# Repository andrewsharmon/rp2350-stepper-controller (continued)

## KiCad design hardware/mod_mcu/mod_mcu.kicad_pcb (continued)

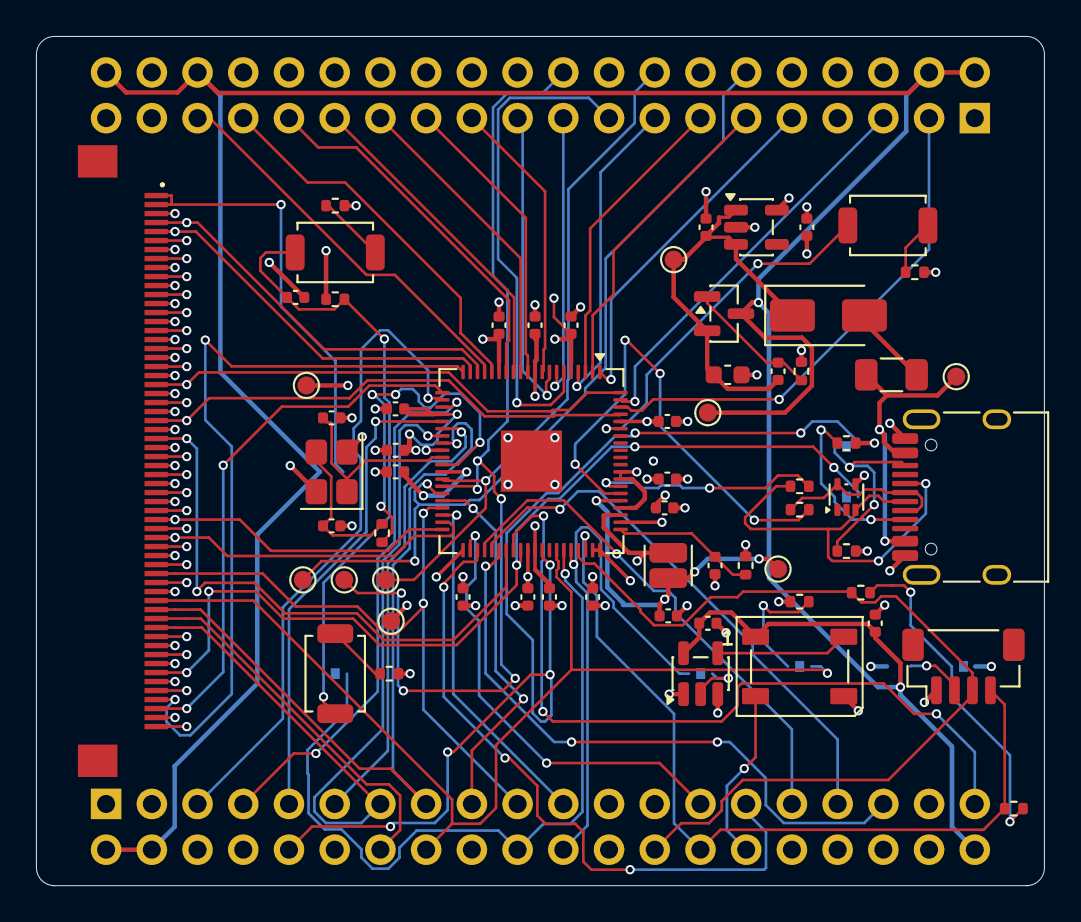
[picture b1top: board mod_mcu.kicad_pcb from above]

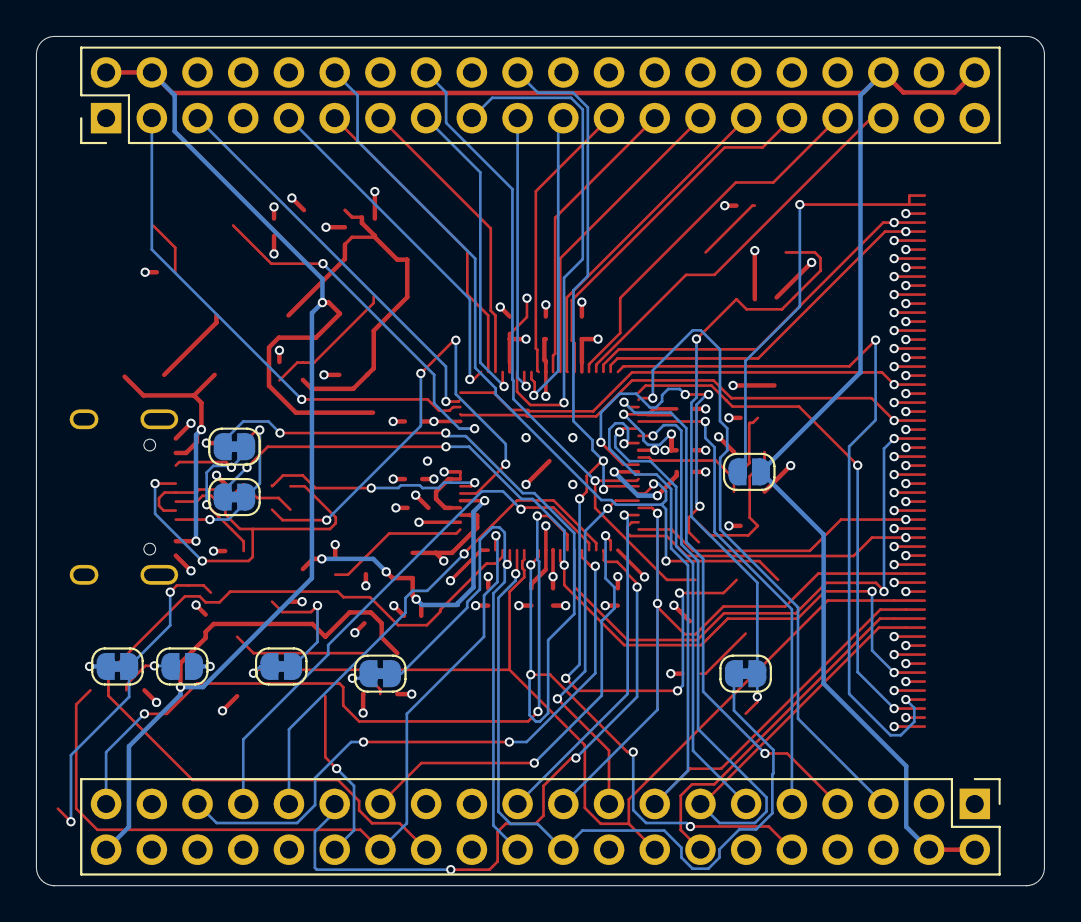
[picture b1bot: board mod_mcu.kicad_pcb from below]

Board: 4 copper layers, 56.0 x 47.2 mm, 73 parts (10 on the bottom side), 82 nets.

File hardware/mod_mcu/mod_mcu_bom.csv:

"Refs","Value","Footprint","Qty","MPN","LCSC","Note"
"C1-C9,C11-C13,C22-C24","100n","Capacitor_SMD:C_0402_1005Metric","15","CL05B104KO5NNNC","C1525",""
"C10,C14,C15","4.7u","Capacitor_SMD:C_0402_1005Metric","3","CL05A475MP5NRNC","C23733",""
"C16,C17","15p","Capacitor_SMD:C_0402_1005Metric","2","0402CG150J500NT","C1548",""
"C18","10u","Capacitor_SMD:C_0603_1608Metric","1","CL10A106KP8NNNC","C19702",""
"C19,C21","1u","Capacitor_SMD:C_0402_1005Metric","2","CL05A105KA5NQNC","C52923",""
"C20","100n","Capacitor_SMD:C_0402_1005Metric","1","CL05B104KO5NNNC","C1525","soft-start timing with the 100k"
"D1","SS54","Diode_SMD:D_SMA","1","SS54","C22452","MDD; Vf 0.55 V @ 5 A (every basic >= 2 A Schottky is SMA)"
"D2","XL-5050RGBC-2812B","LED_SMD:LED_WS2812B_PLCC4_5.0x5.0mm_P3.2mm","1","XL-5050RGBC-2812B","C2843785","XINGLIGHT WS2812B 5050; JLCPCB Standard-PCBA only: hand-solder on Economic"
"F1","1.5A hold","Fuse:Fuse_1206_3216Metric","1","SMD1206B150TFT","C269120","PTTC; 1.5 A hold / 3 A trip, 8 V; 1206 for room"
"J1","USB-C","Connector_USB:USB_C_Receptacle_HRO_TYPE-C-31-M-12","1","TYPE-C-31-M-12","C165948","THT shell legs"
"J2","Qwiic","Connector_JST:JST_SH_BM04B-SRSS-TB_1x04-1MP_P1.00mm_Vertical","1","BM04B-SRSS-TB","C160390",""
"J4","2x20 male","Connector_PinHeader_2.54mm:PinHeader_2x20_P2.54mm_Vertical","1","PZ254-2-20-Z-8.5","C3012260","mod bus A, board underside"
"J5","2x20 male","Connector_PinHeader_2.54mm:PinHeader_2x20_P2.54mm_Vertical","1","PZ254-2-20-Z-8.5","C3012260","mod bus B, board underside"
"J6","FFC 60P","stack:FFC_0.5mm_60P_FlipTop","1","05A20L60P","C22435645","HanElectricity 0.5 mm flip-top; footprint from Hirose FH12, check against its drawing"
"L1","3.3u","Inductor_SMD:L_Cenker_CKCS201610","1","AOTA-B201610S3R3-101-T","C42411119","Abracon part per RP2350 design guide; dot at the +1V1 end, as on the Pico 2"
"Q1","AO3401A","Package_TO_SOT_SMD:SOT-23","1","AO3401A","C15127","AOS; 60 mohm @ 4.5 V, Vth ~0.9 V"
"R1","33","Resistor_SMD:R_0402_1005Metric","1","0402WGF330JTCE","C25105",""
"R2,R13","1k","Resistor_SMD:R_0402_1005Metric","2","0402WGF1001TCE","C11702",""
"R3,R4","22","Resistor_SMD:R_0402_1005Metric","2","0402WGF220JTCE","C25092",""
"R5,R6","5.1k","Resistor_SMD:R_0402_1005Metric","2","0402WGF5101TCE","C25905",""
"R7","100k","Resistor_SMD:R_0402_1005Metric","1","0402WGF1003TCE","C25741","soft-start timing with the 100n"
"R8,R9","4.7k","Resistor_SMD:R_0402_1005Metric","2","0402WGF4701TCE","C25900",""
"R10,R11,R14","10k 1%","Resistor_SMD:R_0402_1005Metric","3","0402WGF1002TCE","C25744",""
"R12","3.3k 1%","Resistor_SMD:R_0402_1005Metric","1","0402WGF3301TCE","C25890",""
"SW1","BTN1","Button_Switch_SMD:SW_SPST_TS-1088-xR020","1","TS-1088-AR02016","C720477","XUNPU 3.9x3.0 mm 2-pad"
"SW2","BTN2","Button_Switch_SMD:SW_SPST_TS-1088-xR020","1","TS-1088-AR02016","C720477","XUNPU 3.9x3.0 mm 2-pad"
"SW3","BOOTSEL","Button_Switch_SMD:SW_SPST_TS-1088-xR020","1","TS-1088-AR02016","C720477","XUNPU 3.9x3.0 mm 2-pad, same as BTN1/BTN2"
"U1","RP2354B","Package_DFN_QFN:QFN-80-1EP_10x10mm_P0.4mm_EP3.4x3.4mm","1","RP2354B","C39843328","2 MB in-package flash; leave QSPI_SD0-3/SCLK unconnected"
"U2","TPD2E2U06","Package_TO_SOT_SMD:SOT-553","1","TPD2E2U06DRLR","C1972959","TI; 1.5 pF; pins 1-2 NC"
"U3","ME6211C33M5G","Package_TO_SOT_SMD:SOT-23-5","1","ME6211C33M5G-N","C82942",""
"U4","74AHCT1G125","Package_TO_SOT_SMD:SOT-23-5","1","SN74AHCT1G125DBVR","C7484",""
"Y1","12MHz","Crystal:Crystal_SMD_3225-4Pin_3.2x2.5mm","1","ABM8-272-T3","C20625731","Abracon, per RP2350 design guide; other crystals need retuning and testing"

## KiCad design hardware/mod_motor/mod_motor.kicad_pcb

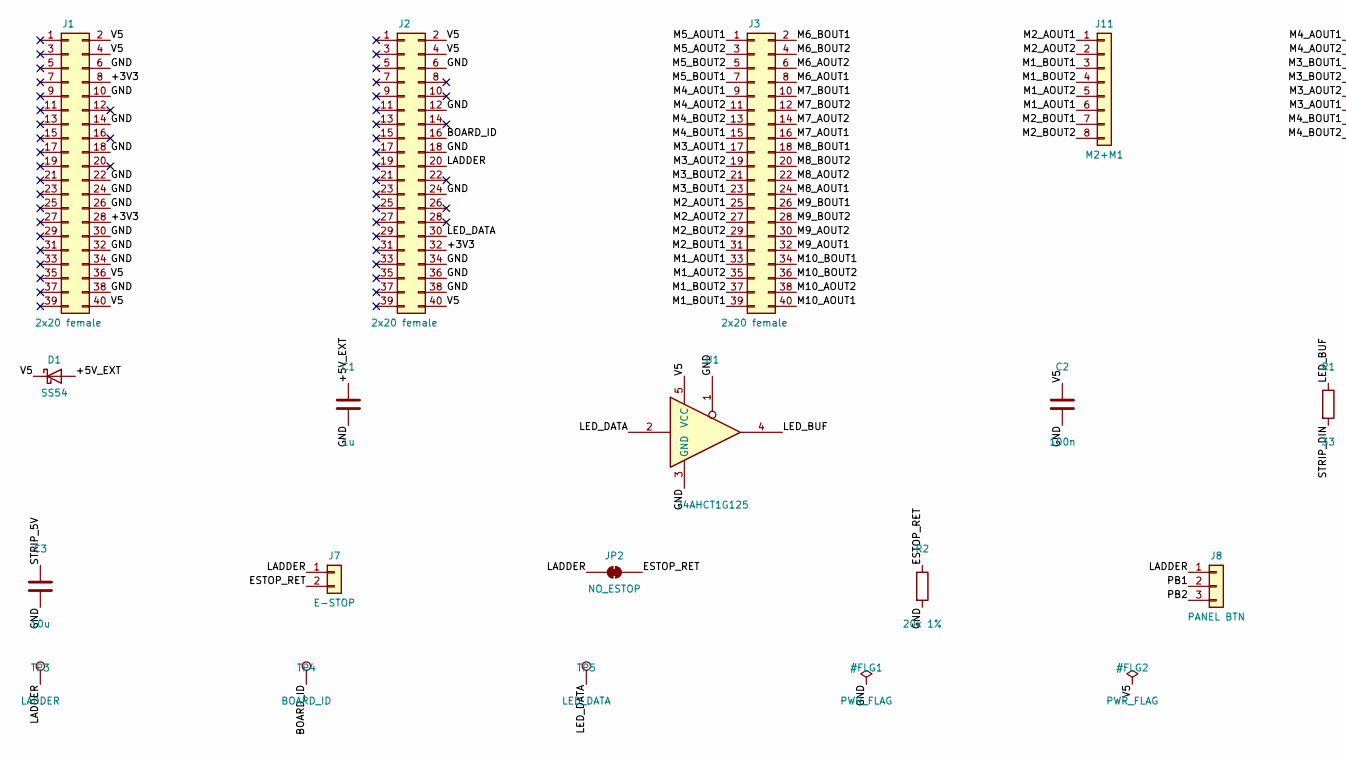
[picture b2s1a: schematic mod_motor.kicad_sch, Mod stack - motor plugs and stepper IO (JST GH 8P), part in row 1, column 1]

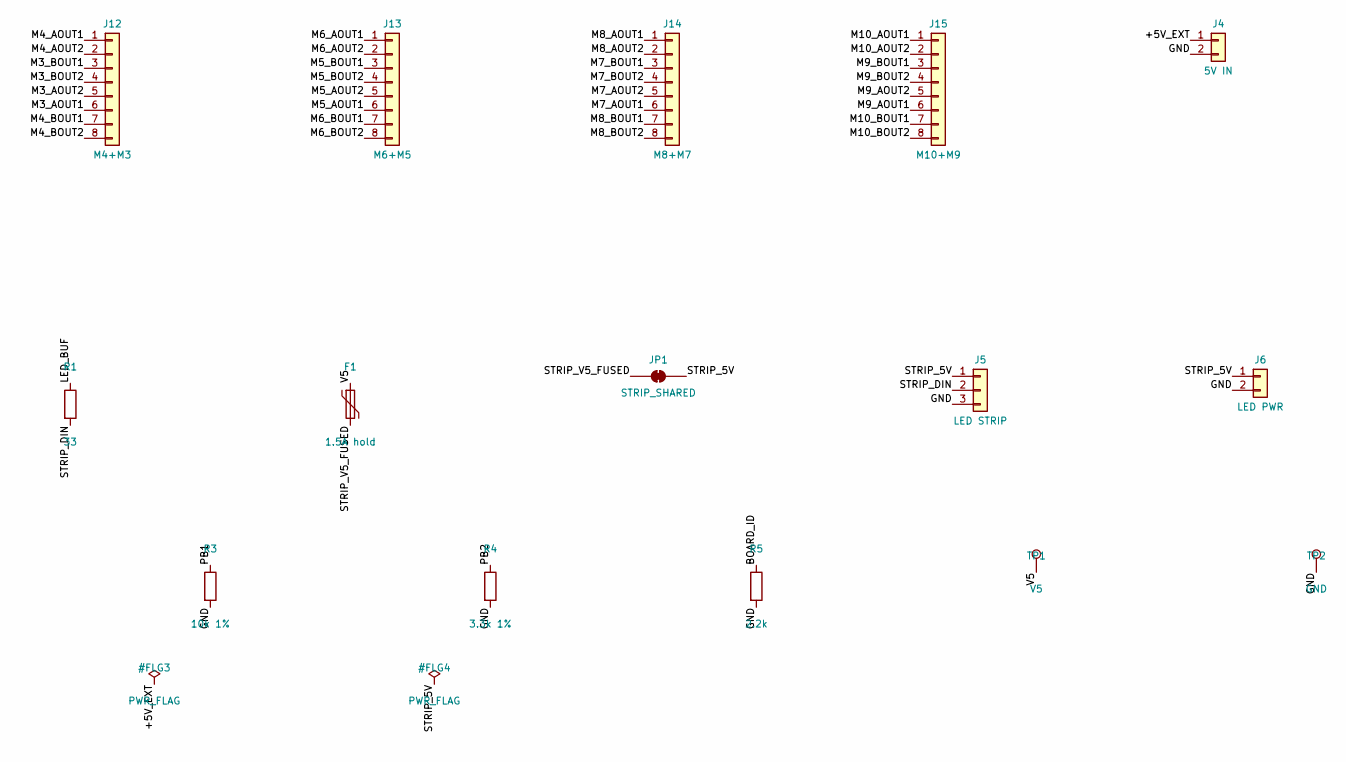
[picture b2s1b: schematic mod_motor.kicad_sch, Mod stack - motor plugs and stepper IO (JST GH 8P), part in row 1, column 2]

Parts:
C1: 1u; C_0402_1005Metric; MPN CL05A105KA5NQNC; LCSC C52923
C2: 100n; C_0402_1005Metric; MPN CL05B104KO5NNNC; LCSC C1525
C3: 10u; C_0603_1608Metric; MPN CL10A106KP8NNNC; LCSC C19702
D1: SS54; D_SMA; MPN SS54; LCSC C22452
F1: 1.5A hold; Fuse_1206_3216Metric; MPN SMD1206B150TFT; LCSC C269120
J1, J2, J3: 2x20 female; PinSocket_2x20_P2.54mm_Vertical; MPN 2.54-2*20P; LCSC C5124634
J4: 5V IN; JST_PH_B2B-PH-K_1x02_P2.00mm_Vertical; MPN B2B-PH-K-S; LCSC C131337
J5: LED STRIP; JST_XH_B3B-XH-A_1x03_P2.50mm_Vertical; MPN B3B-XH-A; LCSC C144394
J6: LED PWR; JST_PH_B2B-PH-K_1x02_P2.00mm_Vertical; MPN B2B-PH-K-S; LCSC C131337
J7: E-STOP; JST_PH_B2B-PH-K_1x02_P2.00mm_Vertical; MPN B2B-PH-K-S; LCSC C131337
J8: PANEL BTN; JST_PH_B3B-PH-K_1x03_P2.00mm_Vertical; MPN B3B-PH-K-S; LCSC C131339
J11: M2+M1; JST_GH_BM08B-GHS-TBT_1x08-1MP_P1.25mm_Vertical; MPN BM08B-GHS-TBT; LCSC C133062
J12: M4+M3; JST_GH_BM08B-GHS-TBT_1x08-1MP_P1.25mm_Vertical; MPN BM08B-GHS-TBT; LCSC C133062
J13: M6+M5; JST_GH_BM08B-GHS-TBT_1x08-1MP_P1.25mm_Vertical; MPN BM08B-GHS-TBT; LCSC C133062
J14: M8+M7; JST_GH_BM08B-GHS-TBT_1x08-1MP_P1.25mm_Vertical; MPN BM08B-GHS-TBT; LCSC C133062
J15: M10+M9; JST_GH_BM08B-GHS-TBT_1x08-1MP_P1.25mm_Vertical; MPN BM08B-GHS-TBT; LCSC C133062
JP1: STRIP_SHARED; SolderJumper-2_P1.3mm_Bridged_RoundedPad1.0x1.5mm
JP2: NO_ESTOP; SolderJumper-2_P1.3mm_Bridged_RoundedPad1.0x1.5mm
R1: 33; R_0402_1005Metric; MPN 0402WGF330JTCE; LCSC C25105
R2: 20k 1%; R_0402_1005Metric; MPN 0402WGF2002TCE; LCSC C25765
R3: 10k 1%; R_0402_1005Metric; MPN 0402WGF1002TCE; LCSC C25744
R4: 3.3k 1%; R_0402_1005Metric; MPN 0402WGF3301TCE; LCSC C25890
R5: 2.2k; R_0402_1005Metric; MPN 0402WGF2201TCE; LCSC C25879
TP1: V5; TestPoint_Pad_D1.0mm
TP2: GND; TestPoint_Pad_D1.0mm
TP3: LADDER; TestPoint_Pad_D1.0mm
TP4: BOARD_ID; TestPoint_Pad_D1.0mm
TP5: LED_DATA; TestPoint_Pad_D1.0mm
U1: 74AHCT1G125; SOT-23-5; MPN SN74AHCT1G125DBVR; LCSC C7484

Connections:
/+3V3: J1.8, J1.28, J2.32
/+5V_EXT: C1.1, D1.2 (A), J4.1
/BOARD_ID: J2.16, R5.1, TP4.1
/ESTOP_RET: J7.2, JP2.2 (B), R2.1
/GND: C1.2, C2.2, C3.2, J1.6, J1.10, J1.14, J1.18, J1.22, J1.24, J1.26, J1.30, J1.32, J1.34, J1.38, J2.6, J2.12, J2.18, J2.24, J2.34, J2.36, J2.38, J4.2, J5.3, J6.2, R2.2, R3.2, R4.2, R5.2, TP2.1, U1.1, U1.3 (GND)
/LADDER: J2.20, J7.1, J8.1, JP2.1 (A), TP3.1
/LED_BUF: R1.1, U1.4
/LED_DATA: J2.30, TP5.1, U1.2
/M1_AOUT1: J3.33, J11.6
/M1_AOUT2: J3.35, J11.5
/M1_BOUT1: J3.39, J11.3
/M1_BOUT2: J3.37, J11.4
/M2_AOUT1: J3.25, J11.1
/M2_AOUT2: J3.27, J11.2
/M2_BOUT1: J3.31, J11.7
/M2_BOUT2: J3.29, J11.8
/M3_AOUT1: J3.17, J12.6
/M3_AOUT2: J3.19, J12.5
/M3_BOUT1: J3.23, J12.3
/M3_BOUT2: J3.21, J12.4
/M4_AOUT1: J3.9, J12.1
/M4_AOUT2: J3.11, J12.2
/M4_BOUT1: J3.15, J12.7
/M4_BOUT2: J3.13, J12.8
/M5_AOUT1: J3.1, J13.6
/M5_AOUT2: J3.3, J13.5
/M5_BOUT1: J3.7, J13.3
/M5_BOUT2: J3.5, J13.4
/M6_AOUT1: J3.8, J13.1
/M6_AOUT2: J3.6, J13.2
/M6_BOUT1: J3.2, J13.7
/M6_BOUT2: J3.4, J13.8
/M7_AOUT1: J3.16, J14.6
/M7_AOUT2: J3.14, J14.5
/M7_BOUT1: J3.10, J14.3
/M7_BOUT2: J3.12, J14.4
/M8_AOUT1: J3.24, J14.1
/M8_AOUT2: J3.22, J14.2
/M8_BOUT1: J3.18, J14.7
/M8_BOUT2: J3.20, J14.8
/M9_AOUT1: J3.32, J15.6
/M9_AOUT2: J3.30, J15.5
/M9_BOUT1: J3.26, J15.3
/M9_BOUT2: J3.28, J15.4
/M10_AOUT1: J3.40, J15.1
/M10_AOUT2: J3.38, J15.2
/M10_BOUT1: J3.34, J15.7
/M10_BOUT2: J3.36, J15.8
/PB1: J8.2, R3.1
/PB2: J8.3, R4.1
/STRIP_5V: C3.1, J5.1, J6.1, JP1.2 (B)
/STRIP_DIN: J5.2, R1.2
/STRIP_V5_FUSED: F1.2, JP1.1 (A)
/V5: C2.1, D1.1 (K), F1.1, J1.2, J1.4, J1.36, J1.40, J2.2, J2.4, J2.40, TP1.1, U1.5 (VCC)

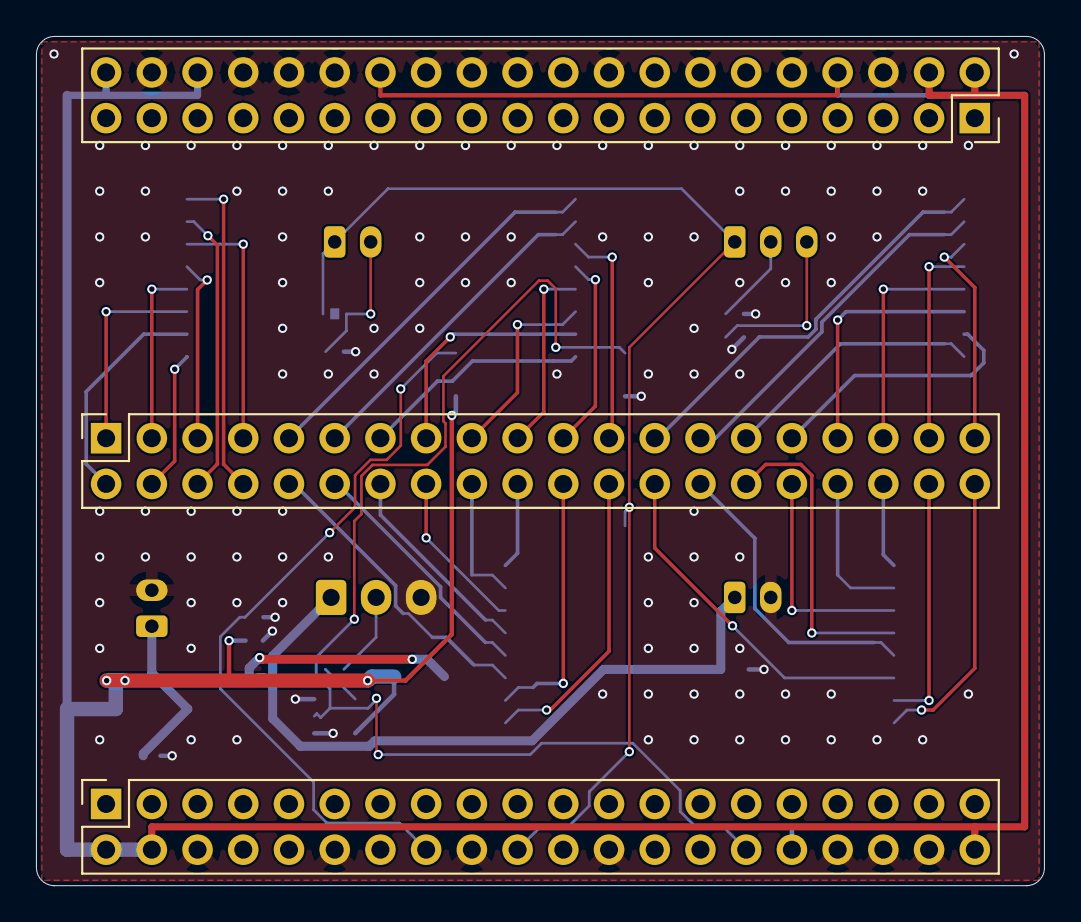
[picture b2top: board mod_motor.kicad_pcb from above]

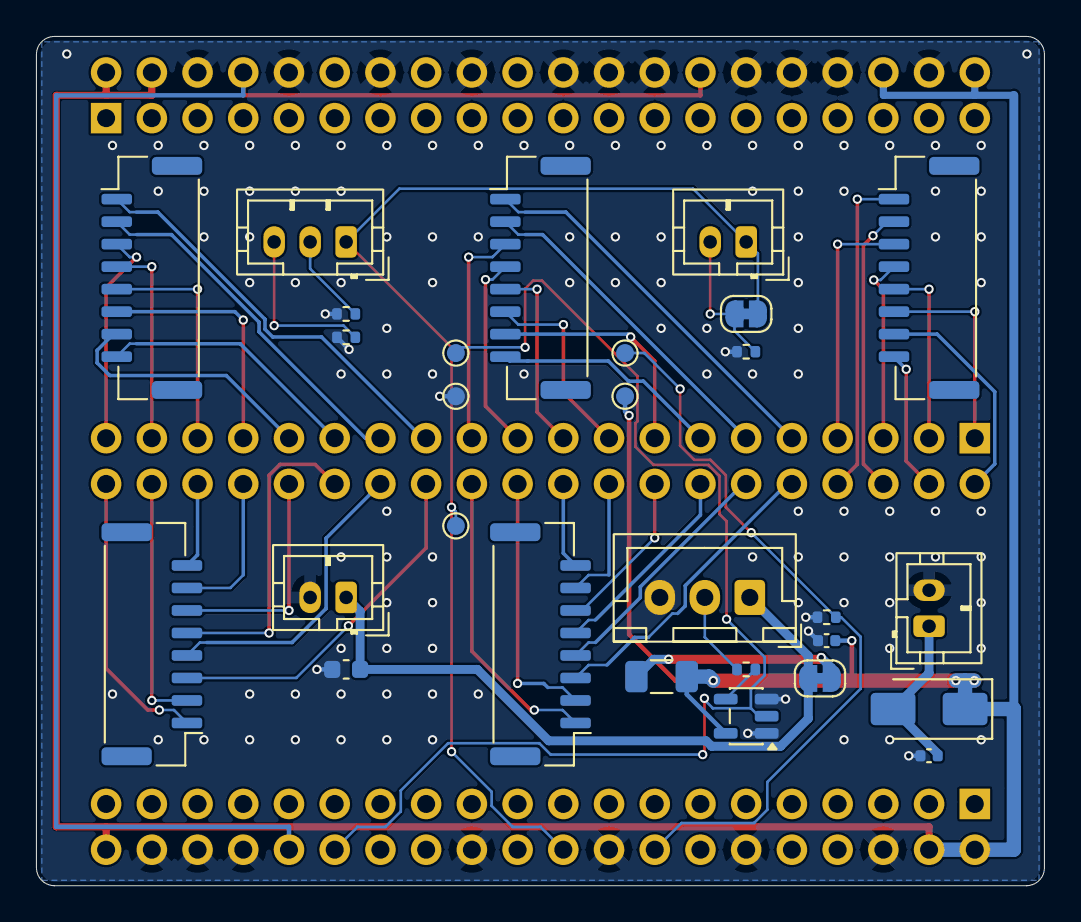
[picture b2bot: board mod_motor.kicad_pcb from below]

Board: 2 copper layers, 56.0 x 47.2 mm, 31 parts (28 on the bottom side), 54 nets.

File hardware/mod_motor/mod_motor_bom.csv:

"Refs","Value","Footprint","Qty","MPN","LCSC","Note"
"C1","1u","Capacitor_SMD:C_0402_1005Metric","1","CL05A105KA5NQNC","C52923",""
"C2","100n","Capacitor_SMD:C_0402_1005Metric","1","CL05B104KO5NNNC","C1525",""
"C3","10u","Capacitor_SMD:C_0603_1608Metric","1","CL10A106KP8NNNC","C19702",""
"D1","SS54","Diode_SMD:D_SMA","1","SS54","C22452","MDD; Vf 0.55 V @ 5 A"
"F1","1.5A hold","Fuse:Fuse_1206_3216Metric","1","SMD1206B150TFT","C269120","PTTC; 1.5 A hold / 3 A trip, 8 V; same part as mod_mcu F1"
"J1","2x20 female","Connector_PinSocket_2.54mm:PinSocket_2x20_P2.54mm_Vertical","1","2.54-2*20P","C5124634","mod bus A, top side"
"J2","2x20 female","Connector_PinSocket_2.54mm:PinSocket_2x20_P2.54mm_Vertical","1","2.54-2*20P","C5124634","mod bus B, top side"
"J3","2x20 female","Connector_PinSocket_2.54mm:PinSocket_2x20_P2.54mm_Vertical","1","2.54-2*20P","C5124634","motor outputs from mod_driver, top side"
"J4","5V IN","Connector_JST:JST_PH_B2B-PH-K_1x02_P2.00mm_Vertical","1","B2B-PH-K-S","C131337",""
"J5","LED STRIP","Connector_JST:JST_XH_B3B-XH-A_1x03_P2.50mm_Vertical","1","B3B-XH-A","C144394",""
"J6","LED PWR","Connector_JST:JST_PH_B2B-PH-K_1x02_P2.00mm_Vertical","1","B2B-PH-K-S","C131337","separate strip supply (optional)"
"J7","E-STOP","Connector_JST:JST_PH_B2B-PH-K_1x02_P2.00mm_Vertical","1","B2B-PH-K-S","C131337",""
"J8","PANEL BTN","Connector_JST:JST_PH_B3B-PH-K_1x03_P2.00mm_Vertical","1","B3B-PH-K-S","C131339","button from pin1 to pin2/pin3"
"J11","M2+M1","Connector_JST:JST_GH_BM08B-GHS-TBT_1x08-1MP_P1.25mm_Vertical","1","BM08B-GHS-TBT","C133062",""
"J12","M4+M3","Connector_JST:JST_GH_BM08B-GHS-TBT_1x08-1MP_P1.25mm_Vertical","1","BM08B-GHS-TBT","C133062",""
"J13","M6+M5","Connector_JST:JST_GH_BM08B-GHS-TBT_1x08-1MP_P1.25mm_Vertical","1","BM08B-GHS-TBT","C133062",""
"J14","M8+M7","Connector_JST:JST_GH_BM08B-GHS-TBT_1x08-1MP_P1.25mm_Vertical","1","BM08B-GHS-TBT","C133062",""
"J15","M10+M9","Connector_JST:JST_GH_BM08B-GHS-TBT_1x08-1MP_P1.25mm_Vertical","1","BM08B-GHS-TBT","C133062",""
"R1","33","Resistor_SMD:R_0402_1005Metric","1","0402WGF330JTCE","C25105",""
"R2","20k 1%","Resistor_SMD:R_0402_1005Metric","1","0402WGF2002TCE","C25765",""
"R3","10k 1%","Resistor_SMD:R_0402_1005Metric","1","0402WGF1002TCE","C25744",""
"R4","3.3k 1%","Resistor_SMD:R_0402_1005Metric","1","0402WGF3301TCE","C25890",""
"R5","2.2k","Resistor_SMD:R_0402_1005Metric","1","0402WGF2201TCE","C25879","board-ID level; 5% ok, see hardware/README.md"
"U1","74AHCT1G125","Package_TO_SOT_SMD:SOT-23-5","1","SN74AHCT1G125DBVR","C7484",""

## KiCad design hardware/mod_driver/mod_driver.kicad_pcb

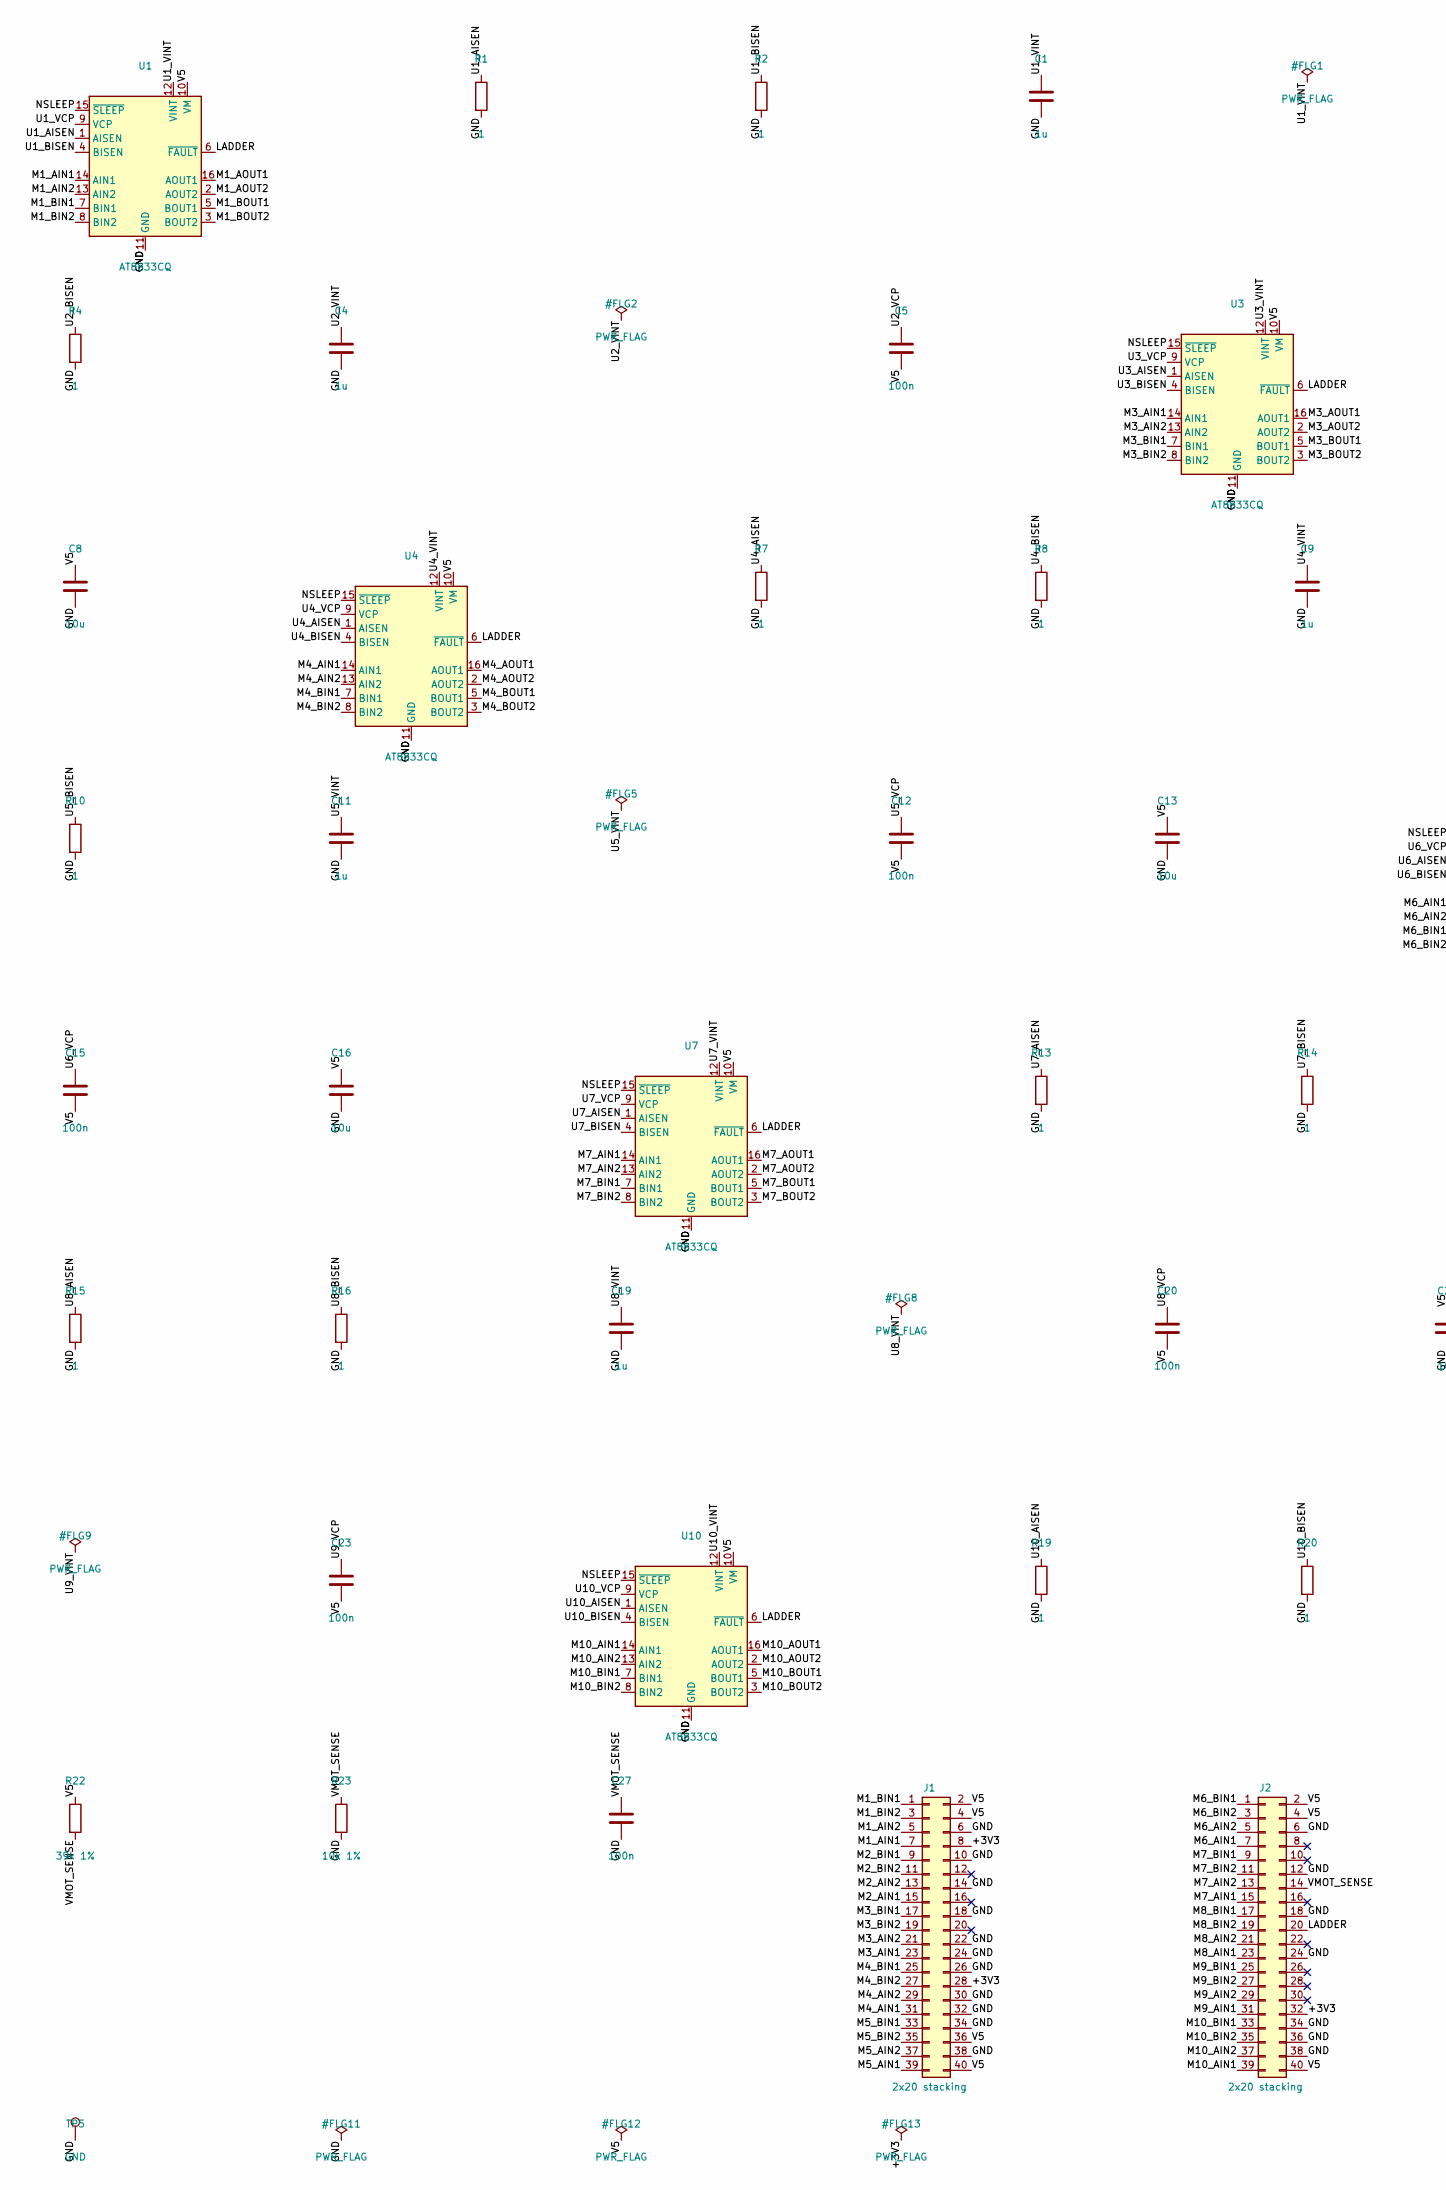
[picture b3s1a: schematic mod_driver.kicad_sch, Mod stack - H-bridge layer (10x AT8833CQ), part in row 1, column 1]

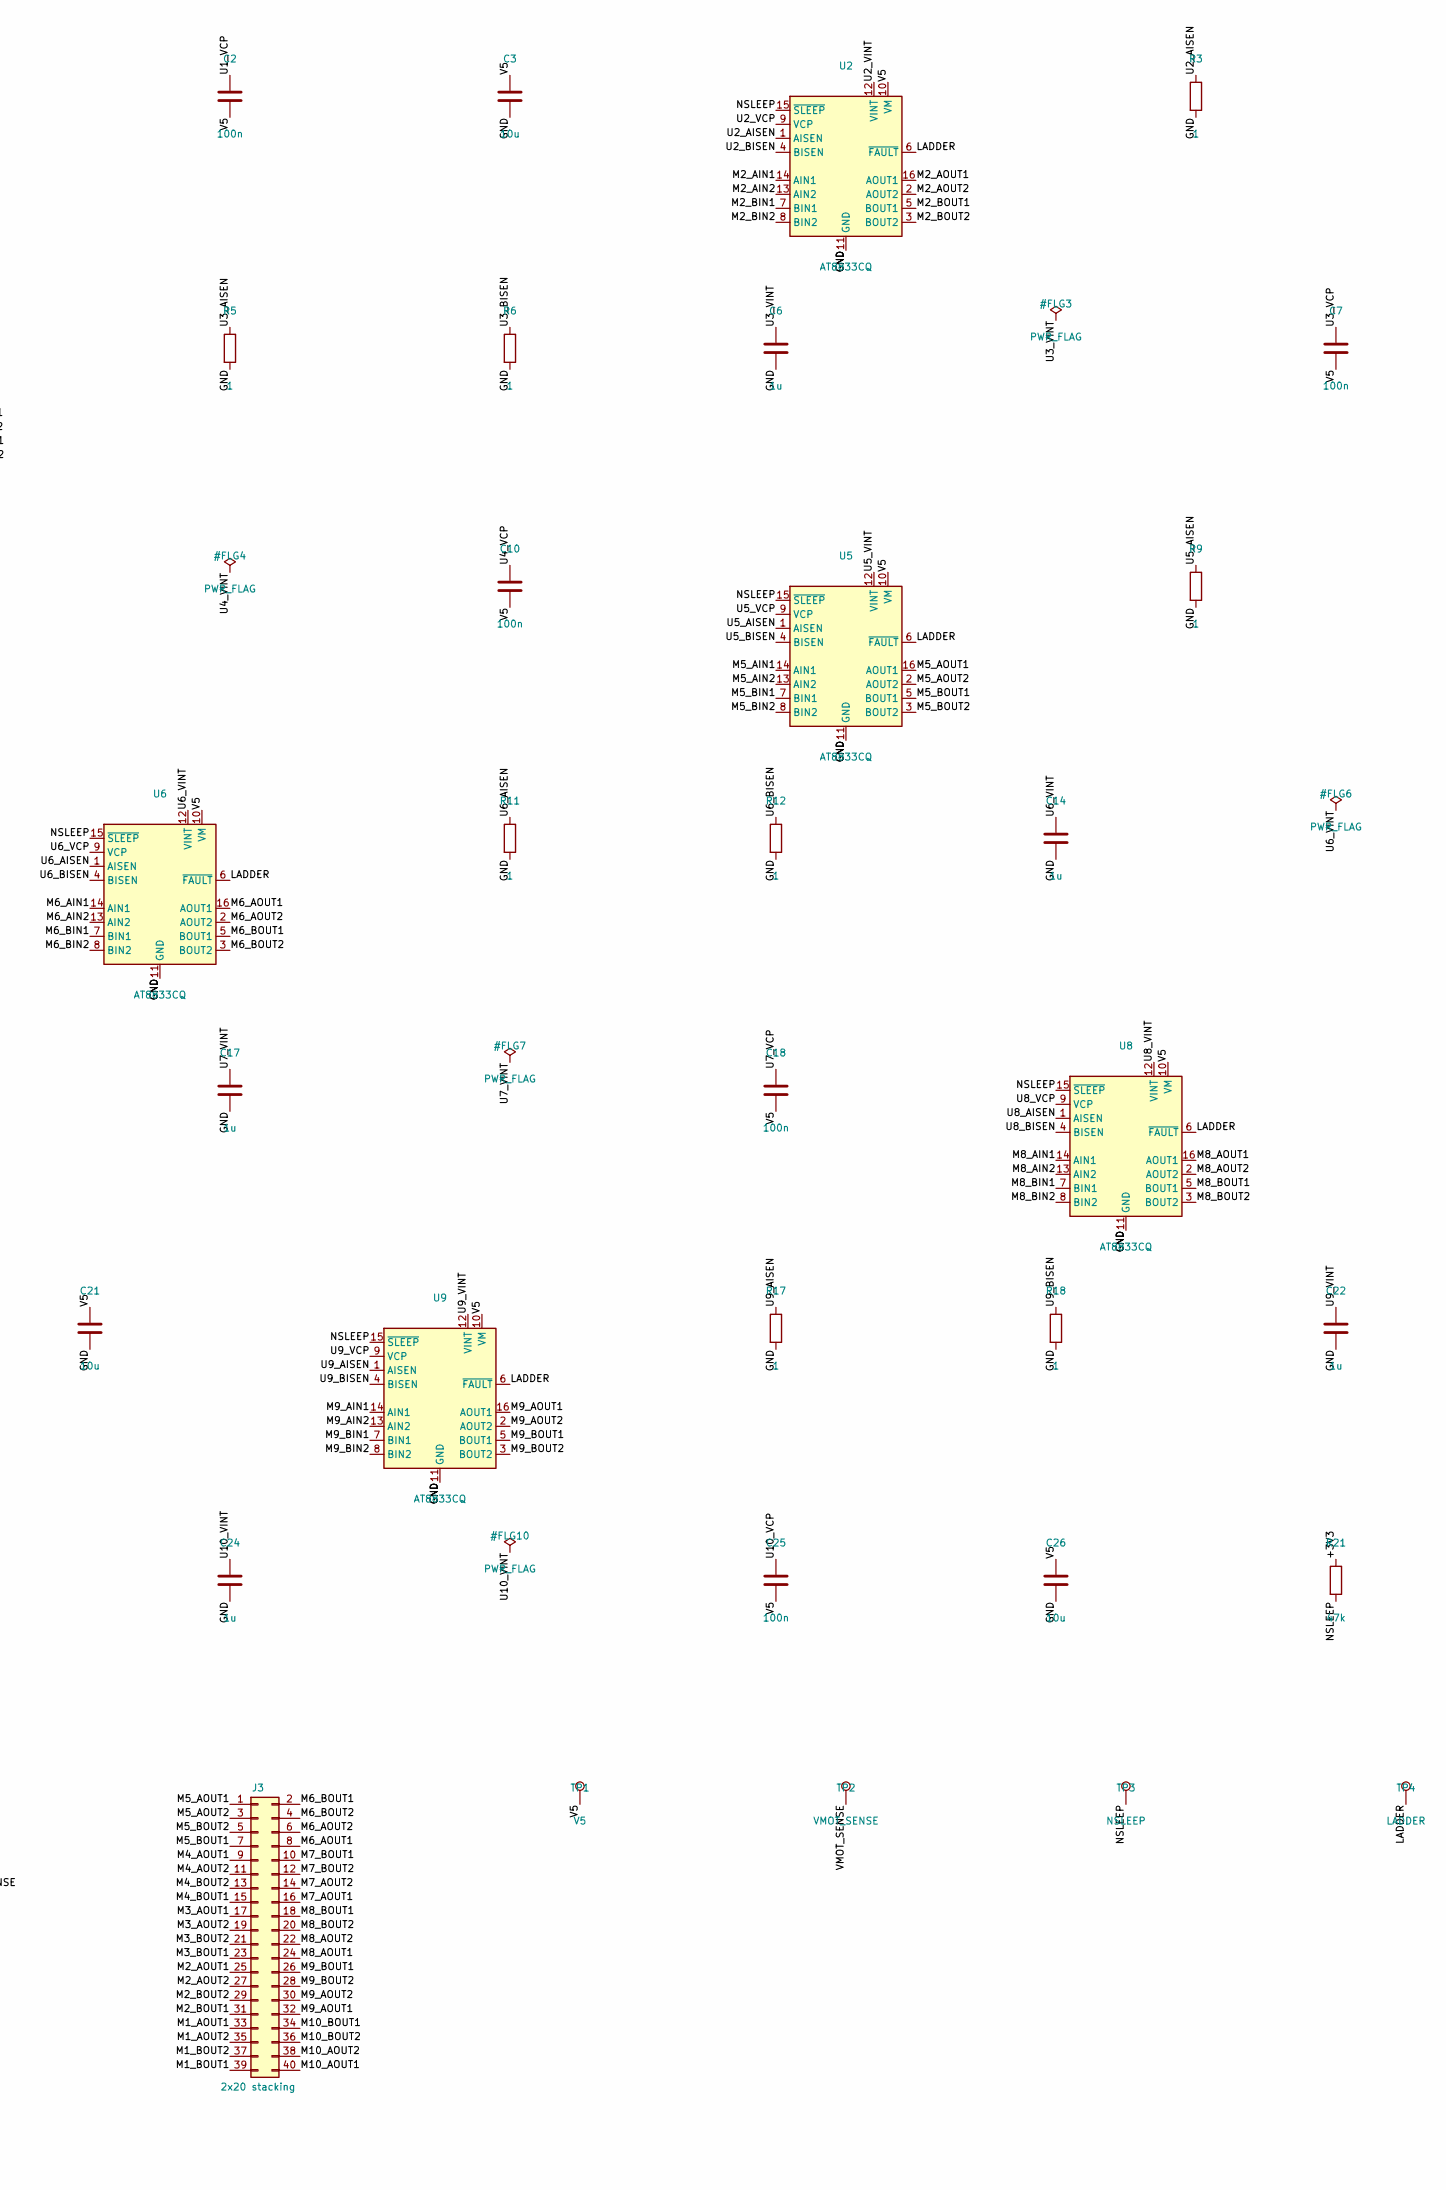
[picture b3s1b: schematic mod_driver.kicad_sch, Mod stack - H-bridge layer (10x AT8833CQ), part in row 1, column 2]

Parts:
C1, C4, C6, C9, C11, C14, C17, C19, C22, C24: 1u; C_0402_1005Metric; MPN CL05A105KA5NQNC; LCSC C52923
C2, C5, C7, C10, C12, C15, C18, C20, C23, C25, C27: 100n; C_0402_1005Metric; MPN CL05B104KO5NNNC; LCSC C1525
C3, C8, C13, C16, C21, C26: 10u; C_0603_1608Metric; MPN CL10A106KP8NNNC; LCSC C19702
J1, J2, J3: 2x20 stacking; PinSocket_2x20_P2.54mm_Vertical; MPN 2.54-2*20PFemale longPC104; LCSC C35165
R1, R2, R3, R4, R5, R6, R7, R8, R9, R10, R11, R12, R13, R14, R15, R16, R17, R18, R19, R20: 1; R_0603_1608Metric; MPN 0603WAF100KT5E; LCSC C22936
R21: 47k; R_0402_1005Metric; MPN 0402WGF4702TCE; LCSC C25792
R22: 39k 1%; R_0603_1608Metric; MPN 0603WAF3902T5E; LCSC C23153
R23: 10k 1%; R_0402_1005Metric; MPN 0402WGF1002TCE; LCSC C25744
TP1: V5; TestPoint_Pad_D1.0mm
TP2: VMOT_SENSE; TestPoint_Pad_D1.0mm
TP3: NSLEEP; TestPoint_Pad_D1.0mm
TP4: LADDER; TestPoint_Pad_D1.0mm
TP5: GND; TestPoint_Pad_D1.0mm
U1, U2, U3, U4, U5, U6, U7, U8, U9, U10: AT8833CQ; QFN-16-1EP_4x4mm_P0.65mm_EP2.1x2.1mm; MPN AT8833CQ; LCSC C5120769

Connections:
/+3V3: J1.8, J1.28, J2.32, R21.1
/GND: C1.2, C3.2, C4.2, C6.2, C8.2, C9.2, C11.2, C13.2, C14.2, C16.2, C17.2, C19.2, C21.2, C22.2, C24.2, C26.2, C27.2, J1.6, J1.10, J1.14, J1.18, J1.22, J1.24, J1.26, J1.30, J1.32, J1.34, J1.38, J2.6, J2.12, J2.18, J2.24, J2.34, J2.36, J2.38, R1.2, R2.2, R3.2, R4.2, R5.2, R6.2, R7.2, R8.2, R9.2, R10.2, R11.2, R12.2, R13.2, R14.2, R15.2, R16.2, R17.2, R18.2, R19.2, R20.2, R23.2, TP5.1, U1.11 (GND), U1.17 (GND), U2.11 (GND), U2.17 (GND), U3.11 (GND), U3.17 (GND), U4.11 (GND), U4.17 (GND), U5.11 (GND), U5.17 (GND), U6.11 (GND), U6.17 (GND), U7.11 (GND), U7.17 (GND), U8.11 (GND), U8.17 (GND), U9.11 (GND), U9.17 (GND), U10.11 (GND), U10.17 (GND)
/LADDER: J2.20, TP4.1, U1.6 (~FAULT), U2.6 (~FAULT), U3.6 (~FAULT), U4.6 (~FAULT), U5.6 (~FAULT), U6.6 (~FAULT), U7.6 (~FAULT), U8.6 (~FAULT), U9.6 (~FAULT), U10.6 (~FAULT)
/M1_AIN1: J1.7, U1.14 (AIN1)
/M1_AIN2: J1.5, U1.13 (AIN2)
/M1_AOUT1: J3.33, U1.16 (AOUT1)
/M1_AOUT2: J3.35, U1.2 (AOUT2)
/M1_BIN1: J1.1, U1.7 (BIN1)
/M1_BIN2: J1.3, U1.8 (BIN2)
/M1_BOUT1: J3.39, U1.5 (BOUT1)
/M1_BOUT2: J3.37, U1.3 (BOUT2)
/M2_AIN1: J1.15, U2.14 (AIN1)
/M2_AIN2: J1.13, U2.13 (AIN2)
/M2_AOUT1: J3.25, U2.16 (AOUT1)
/M2_AOUT2: J3.27, U2.2 (AOUT2)
/M2_BIN1: J1.9, U2.7 (BIN1)
/M2_BIN2: J1.11, U2.8 (BIN2)
/M2_BOUT1: J3.31, U2.5 (BOUT1)
/M2_BOUT2: J3.29, U2.3 (BOUT2)
/M3_AIN1: J1.23, U3.14 (AIN1)
/M3_AIN2: J1.21, U3.13 (AIN2)
/M3_AOUT1: J3.17, U3.16 (AOUT1)
/M3_AOUT2: J3.19, U3.2 (AOUT2)
/M3_BIN1: J1.17, U3.7 (BIN1)
/M3_BIN2: J1.19, U3.8 (BIN2)
/M3_BOUT1: J3.23, U3.5 (BOUT1)
/M3_BOUT2: J3.21, U3.3 (BOUT2)
/M4_AIN1: J1.31, U4.14 (AIN1)
/M4_AIN2: J1.29, U4.13 (AIN2)
/M4_AOUT1: J3.9, U4.16 (AOUT1)
/M4_AOUT2: J3.11, U4.2 (AOUT2)
/M4_BIN1: J1.25, U4.7 (BIN1)
/M4_BIN2: J1.27, U4.8 (BIN2)
/M4_BOUT1: J3.15, U4.5 (BOUT1)
/M4_BOUT2: J3.13, U4.3 (BOUT2)
/M5_AIN1: J1.39, U5.14 (AIN1)
/M5_AIN2: J1.37, U5.13 (AIN2)
/M5_AOUT1: J3.1, U5.16 (AOUT1)
/M5_AOUT2: J3.3, U5.2 (AOUT2)
/M5_BIN1: J1.33, U5.7 (BIN1)
/M5_BIN2: J1.35, U5.8 (BIN2)
/M5_BOUT1: J3.7, U5.5 (BOUT1)
/M5_BOUT2: J3.5, U5.3 (BOUT2)
/M6_AIN1: J2.7, U6.14 (AIN1)
/M6_AIN2: J2.5, U6.13 (AIN2)
/M6_AOUT1: J3.8, U6.16 (AOUT1)
/M6_AOUT2: J3.6, U6.2 (AOUT2)
/M6_BIN1: J2.1, U6.7 (BIN1)
/M6_BIN2: J2.3, U6.8 (BIN2)
/M6_BOUT1: J3.2, U6.5 (BOUT1)
/M6_BOUT2: J3.4, U6.3 (BOUT2)
/M7_AIN1: J2.15, U7.14 (AIN1)
/M7_AIN2: J2.13, U7.13 (AIN2)
/M7_AOUT1: J3.16, U7.16 (AOUT1)
/M7_AOUT2: J3.14, U7.2 (AOUT2)
/M7_BIN1: J2.9, U7.7 (BIN1)
/M7_BIN2: J2.11, U7.8 (BIN2)
/M7_BOUT1: J3.10, U7.5 (BOUT1)
/M7_BOUT2: J3.12, U7.3 (BOUT2)
/M8_AIN1: J2.23, U8.14 (AIN1)
/M8_AIN2: J2.21, U8.13 (AIN2)
/M8_AOUT1: J3.24, U8.16 (AOUT1)
/M8_AOUT2: J3.22, U8.2 (AOUT2)
/M8_BIN1: J2.17, U8.7 (BIN1)
/M8_BIN2: J2.19, U8.8 (BIN2)
/M8_BOUT1: J3.18, U8.5 (BOUT1)
/M8_BOUT2: J3.20, U8.3 (BOUT2)
/M9_AIN1: J2.31, U9.14 (AIN1)
/M9_AIN2: J2.29, U9.13 (AIN2)
/M9_AOUT1: J3.32, U9.16 (AOUT1)
/M9_AOUT2: J3.30, U9.2 (AOUT2)
/M9_BIN1: J2.25, U9.7 (BIN1)
/M9_BIN2: J2.27, U9.8 (BIN2)
/M9_BOUT1: J3.26, U9.5 (BOUT1)
/M9_BOUT2: J3.28, U9.3 (BOUT2)
/M10_AIN1: J2.39, U10.14 (AIN1)
/M10_AIN2: J2.37, U10.13 (AIN2)
/M10_AOUT1: J3.40, U10.16 (AOUT1)
/M10_AOUT2: J3.38, U10.2 (AOUT2)
/M10_BIN1: J2.33, U10.7 (BIN1)
/M10_BIN2: J2.35, U10.8 (BIN2)
/M10_BOUT1: J3.34, U10.5 (BOUT1)
/M10_BOUT2: J3.36, U10.3 (BOUT2)
/NSLEEP: R21.2, TP3.1, U1.15 (~SLEEP), U2.15 (~SLEEP), U3.15 (~SLEEP), U4.15 (~SLEEP), U5.15 (~SLEEP), U6.15 (~SLEEP), U7.15 (~SLEEP), U8.15 (~SLEEP), U9.15 (~SLEEP), U10.15 (~SLEEP)
/U1_AISEN: R1.1, U1.1 (AISEN)
/U1_BISEN: R2.1, U1.4 (BISEN)
/U1_VCP: C2.1, U1.9 (VCP)
/U1_VINT: C1.1, U1.12 (VINT)
/U2_AISEN: R3.1, U2.1 (AISEN)
/U2_BISEN: R4.1, U2.4 (BISEN)
/U2_VCP: C5.1, U2.9 (VCP)
/U2_VINT: C4.1, U2.12 (VINT)
/U3_AISEN: R5.1, U3.1 (AISEN)
/U3_BISEN: R6.1, U3.4 (BISEN)
/U3_VCP: C7.1, U3.9 (VCP)
/U3_VINT: C6.1, U3.12 (VINT)
/U4_AISEN: R7.1, U4.1 (AISEN)
/U4_BISEN: R8.1, U4.4 (BISEN)
/U4_VCP: C10.1, U4.9 (VCP)
/U4_VINT: C9.1, U4.12 (VINT)
/U5_AISEN: R9.1, U5.1 (AISEN)
/U5_BISEN: R10.1, U5.4 (BISEN)
/U5_VCP: C12.1, U5.9 (VCP)
/U5_VINT: C11.1, U5.12 (VINT)
/U6_AISEN: R11.1, U6.1 (AISEN)
/U6_BISEN: R12.1, U6.4 (BISEN)
/U6_VCP: C15.1, U6.9 (VCP)
/U6_VINT: C14.1, U6.12 (VINT)
/U7_AISEN: R13.1, U7.1 (AISEN)
/U7_BISEN: R14.1, U7.4 (BISEN)
/U7_VCP: C18.1, U7.9 (VCP)
/U7_VINT: C17.1, U7.12 (VINT)
/U8_AISEN: R15.1, U8.1 (AISEN)
/U8_BISEN: R16.1, U8.4 (BISEN)
/U8_VCP: C20.1, U8.9 (VCP)
/U8_VINT: C19.1, U8.12 (VINT)
/U9_AISEN: R17.1, U9.1 (AISEN)
/U9_BISEN: R18.1, U9.4 (BISEN)
/U9_VCP: C23.1, U9.9 (VCP)
/U9_VINT: C22.1, U9.12 (VINT)
/U10_AISEN: R19.1, U10.1 (AISEN)
/U10_BISEN: R20.1, U10.4 (BISEN)
/U10_VCP: C25.1, U10.9 (VCP)
/U10_VINT: C24.1, U10.12 (VINT)
/V5: C2.2, C3.1, C5.2, C7.2, C8.1, C10.2, C12.2, C13.1, C15.2, C16.1, C18.2, C20.2, C21.1, C23.2, C25.2, C26.1, J1.2, J1.4, J1.36, J1.40, J2.2, J2.4, J2.40, R22.1, TP1.1, U1.10 (VM), U2.10 (VM), U3.10 (VM), U4.10 (VM), U5.10 (VM), U6.10 (VM), U7.10 (VM), U8.10 (VM), U9.10 (VM), U10.10 (VM)
/VMOT_SENSE: C27.1, J2.14, R22.2, R23.1, TP2.1
